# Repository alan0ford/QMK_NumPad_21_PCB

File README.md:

## PCB 21 Surplus NumPad

PCB wired, cheaper mechanical NumPad with scraps.

- Case: in plywood [handmade](https://i.imgur.com/z5PfJda.jpg)
- PCB: [front](https://i.imgur.com/lKIDMKF.jpg), [rear](https://i.imgur.com/YPauPd1.jpg)
- Keycaps: Akko MDA BOW
- [Switches](https://i.imgur.com/sbnH1w1.jpg): Kailh cream, Cherry black, WS Jade
- MCU: ProMicro clone Atmega32u4

PCB Rear:

## Case 404 (a second, more fashionable version)

- Case: four [wooden](https://i.imgur.com/WyksgFc.jpg) pieces
- PCB: [front](https://i.imgur.com/lKIDMKF.jpg), [rear](https://i.imgur.com/YPauPd1.jpg)
- Keycaps: CRP-X Buger Parallel Worlds
- Switches: Kailh cream
- MCU: ProMicro clone Atmega32u4 USB C

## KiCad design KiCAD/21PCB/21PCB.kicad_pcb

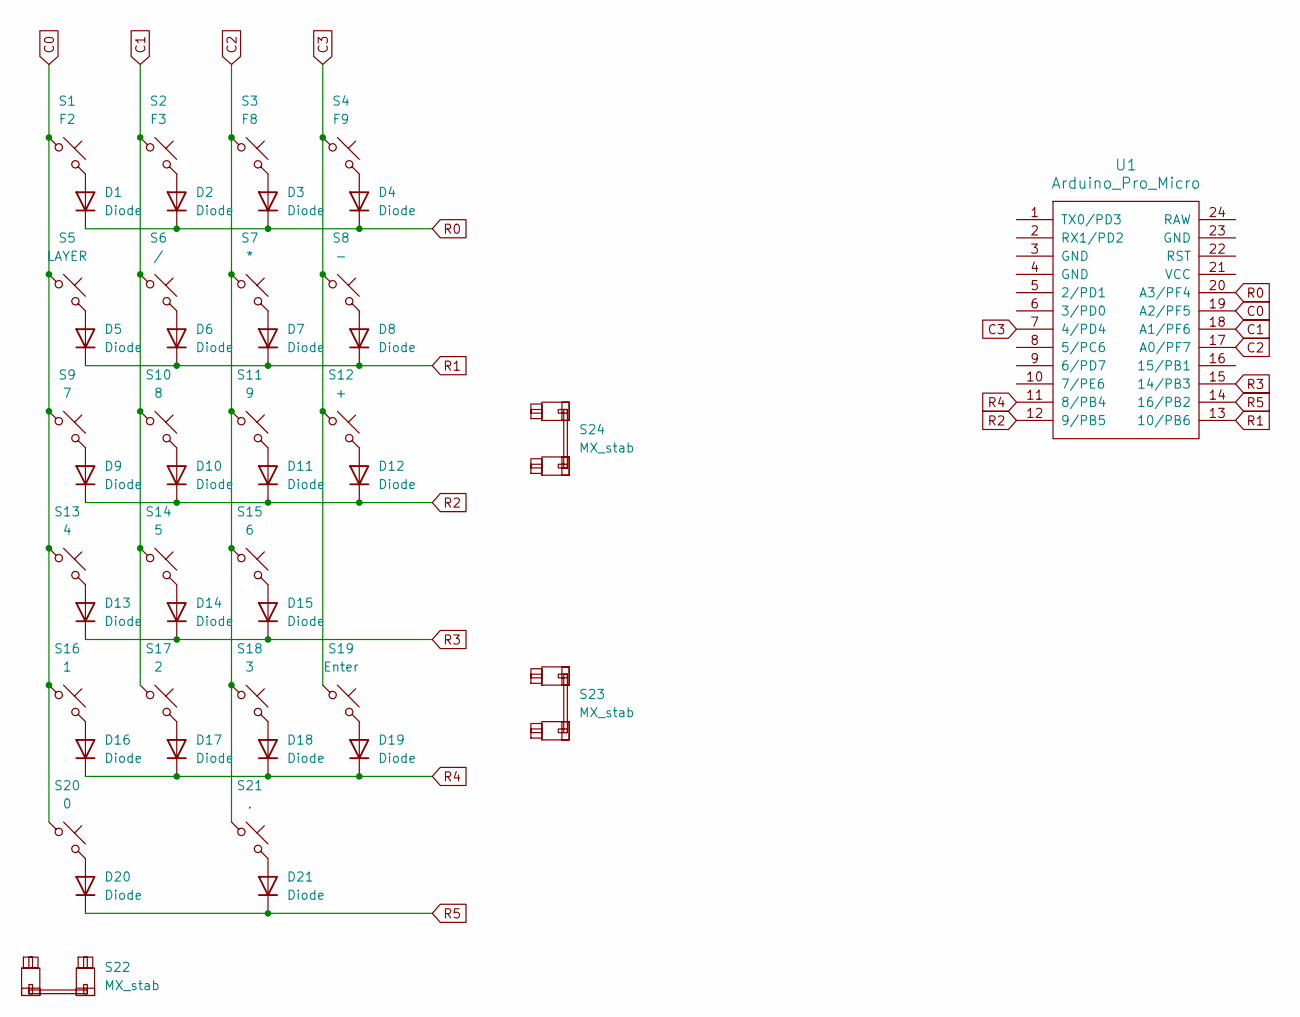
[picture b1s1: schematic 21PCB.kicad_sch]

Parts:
D1, D2, D3, D4, D5, D6, D7, D8, D9, D10, D11, D12, D13, D14, D15, D16, D17, D18, D19, D20, D21: Diode; Diode_DO-35
S1: F2; MX_PCB_1.00u
S2: F3; MX_PCB_1.00u
S3: F8; MX_PCB_1.00u
S4: F9; MX_PCB_1.00u
S5: LAYER; MX_PCB_1.00u
S6: /; MX_PCB_1.00u
S7: *; MX_PCB_1.00u
S8: -; MX_PCB_1.00u
S9: 7; MX_PCB_1.00u
S10: 8; MX_PCB_1.00u
S11: 9; MX_PCB_1.00u
S12: +; MX_PCB_2.00u_90deg
S13: 4; MX_PCB_1.00u
S14: 5; MX_PCB_1.00u
S15: 6; MX_PCB_1.00u
S16: 1; MX_PCB_1.00u
S17: 2; MX_PCB_1.00u
S18: 3; MX_PCB_1.00u
S19: Enter; MX_PCB_2.00u_90deg
S20: 0; MX_PCB_2.00u
S21: .; MX_PCB_1.00u
S22, S23, S24: MX_stab; STAB_MX_2u
U1: Arduino_Pro_Micro

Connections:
C0: S1.1, S5.1, S9.1, S13.1, S16.1, S20.1, U1.19 (A2/PF5)
C1: S2.1, S6.1, S10.1, S14.1, S17.1, U1.18 (A1/PF6)
C2: S3.1, S7.1, S11.1, S15.1, S18.1, S21.1, U1.17 (A0/PF7)
C3: S4.1, S8.1, S12.1, S19.1, U1.7 (4/PD4)
unnamed: D1.2 (A), S1.2
unnamed: D2.2 (A), S2.2
unnamed: D3.2 (A), S3.2
unnamed: D4.2 (A), S4.2
unnamed: D5.2 (A), S5.2
unnamed: D6.2 (A), S6.2
unnamed: D7.2 (A), S7.2
unnamed: D8.2 (A), S8.2
unnamed: D9.2 (A), S9.2
unnamed: D10.2 (A), S10.2
unnamed: D11.2 (A), S11.2
unnamed: D12.2 (A), S12.2
unnamed: D13.2 (A), S13.2
unnamed: D14.2 (A), S14.2
unnamed: D15.2 (A), S15.2
unnamed: D16.2 (A), S16.2
unnamed: D17.2 (A), S17.2
unnamed: D18.2 (A), S18.2
unnamed: D19.2 (A), S19.2
unnamed: D20.2 (A), S20.2
unnamed: D21.2 (A), S21.2
R0: D1.1 (K), D2.1 (K), D3.1 (K), D4.1 (K), U1.20 (A3/PF4)
R1: D5.1 (K), D6.1 (K), D7.1 (K), D8.1 (K), U1.13 (10/PB6)
R2: D9.1 (K), D10.1 (K), D11.1 (K), D12.1 (K), U1.12 (9/PB5)
R3: D13.1 (K), D14.1 (K), D15.1 (K), U1.15 (14/PB3)
R4: D16.1 (K), D17.1 (K), D18.1 (K), D19.1 (K), U1.11 (8/PB4)
R5: D20.1 (K), D21.1 (K), U1.14 (16/PB2)

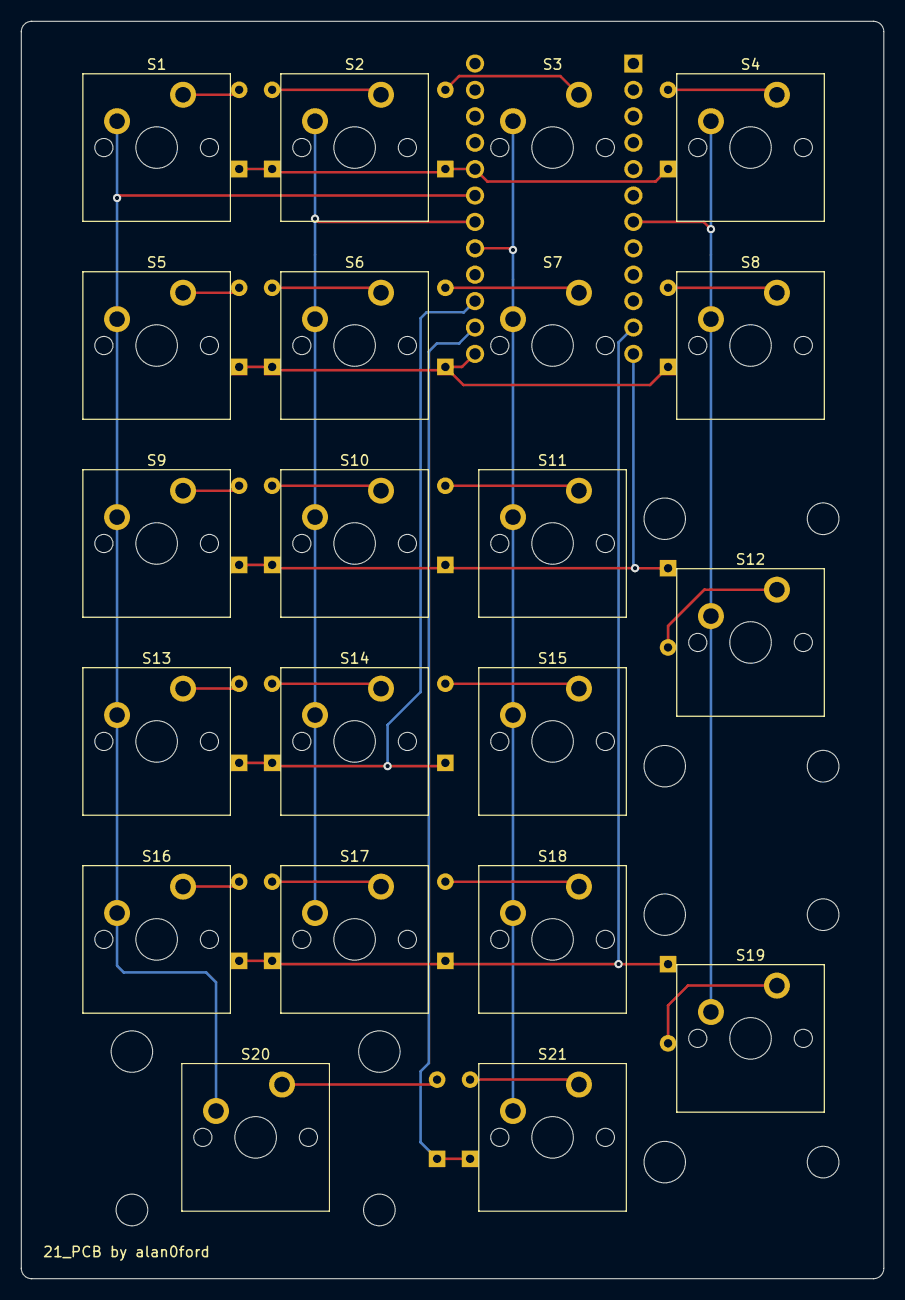
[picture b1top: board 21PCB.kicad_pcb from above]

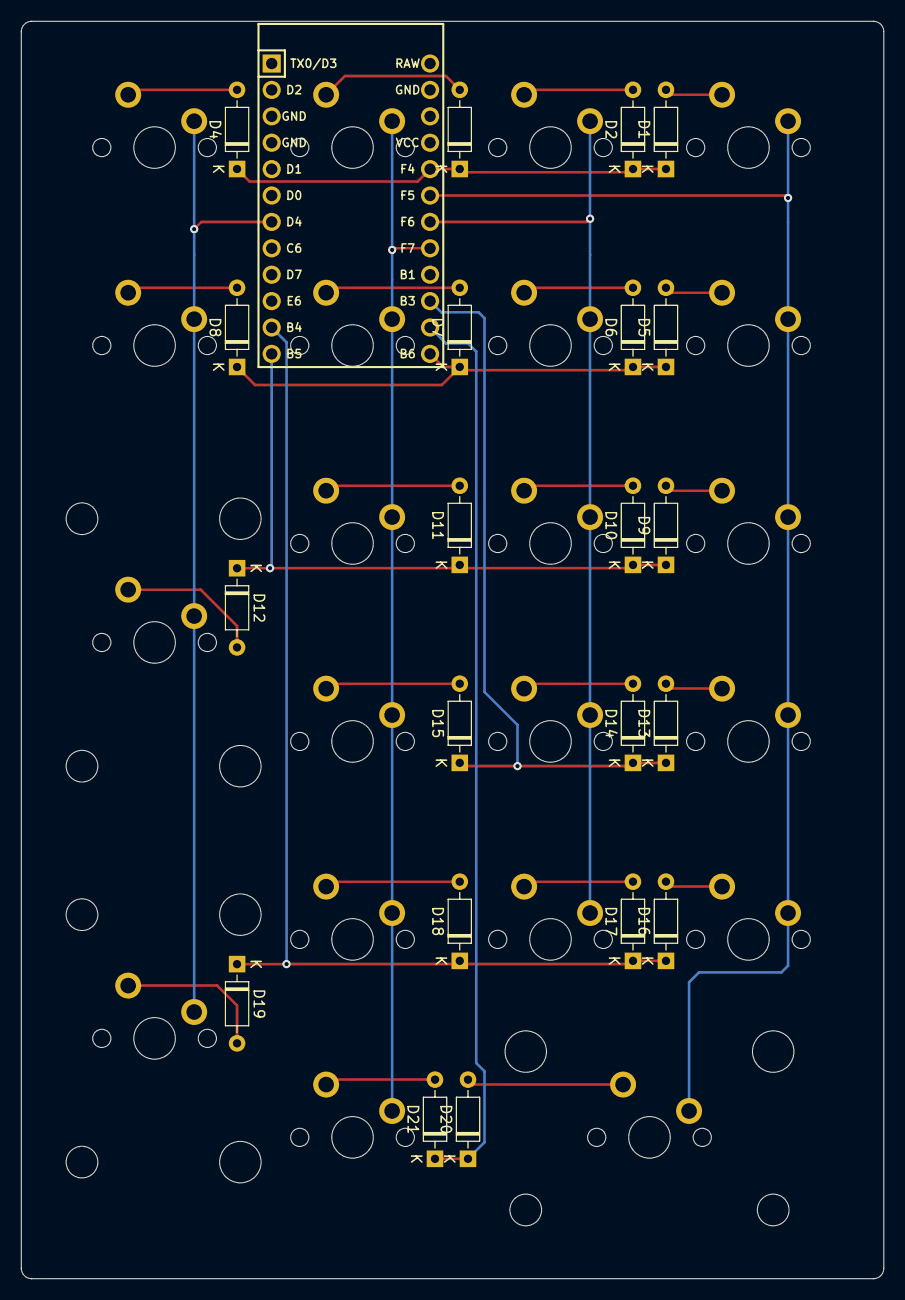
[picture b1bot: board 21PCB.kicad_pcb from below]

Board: 2 copper layers, 83.0 x 121.0 mm, 46 parts (22 on the bottom side), 31 nets.

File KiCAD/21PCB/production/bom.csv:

Designator,Footprint,Quantity,Value,LCSC Part #
"D1, D10, D11, D12, D13, D14, D15, D16, D17, D18, D19, D2, D20, D21, D3, D4, D5, D6, D7, D8, D9",Diode_DO-35,21,Diode,
S1,MX_PCB_1.00u,1,F2,
S10,MX_PCB_1.00u,1,8,
S11,MX_PCB_1.00u,1,9,
S12,MX_PCB_2.00u_90deg,1,+,
S13,MX_PCB_1.00u,1,4,
S14,MX_PCB_1.00u,1,5,
S15,MX_PCB_1.00u,1,6,
S16,MX_PCB_1.00u,1,1,
S17,MX_PCB_1.00u,1,2,
S18,MX_PCB_1.00u,1,3,
S19,MX_PCB_2.00u_90deg,1,Enter,
S2,MX_PCB_1.00u,1,F3,
S20,MX_PCB_2.00u,1,0,
S21,MX_PCB_1.00u,1,.,
"S22, S23, S24",STAB_MX_2u,3,MX_stab,
S3,MX_PCB_1.00u,1,F8,
S4,MX_PCB_1.00u,1,F9,
S5,MX_PCB_1.00u,1,LAYER,
S6,MX_PCB_1.00u,1,/,
S7,MX_PCB_1.00u,1,*,
S8,MX_PCB_1.00u,1,-,
S9,MX_PCB_1.00u,1,7,
U1,Arduino_Pro_Micro,1,Arduino_Pro_Micro,

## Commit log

2024-03-05 File iniziali
2024-03-27 added case404 firmware
